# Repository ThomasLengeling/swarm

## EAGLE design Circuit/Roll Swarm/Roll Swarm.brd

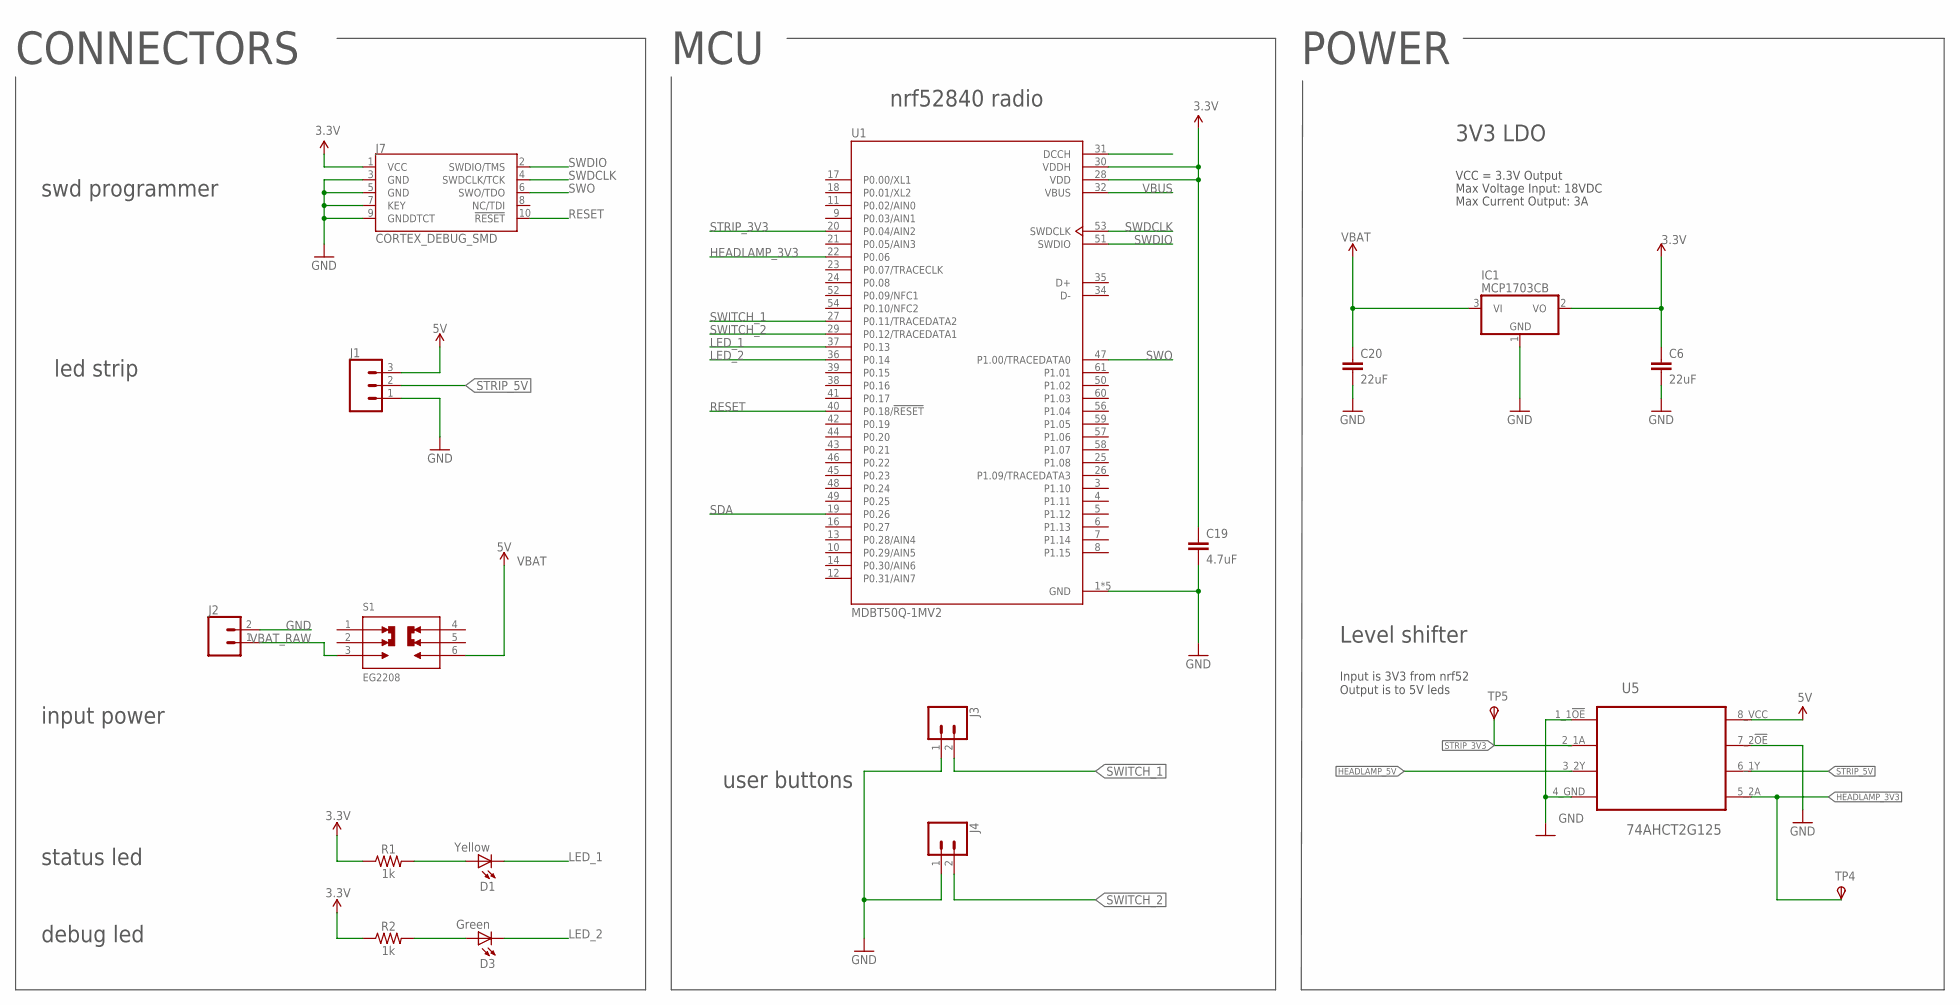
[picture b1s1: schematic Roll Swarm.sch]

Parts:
C6, C20: 22uF; 0805; DIGIKEY 490-10511-1-ND
C19: 4.7uF; 0603; DIGIKEY 399-3482-1-ND
D1: Yellow; LED-0603; DIGIKEY 350-4349-2-ND
D3: Green; LED-0603; DIGIKEY 754-1116-1-ND
IC1: MCP1703CB; SOT23; DIGIKEY AP2138N-3.3TRG1DICT-ND
J1: CONN_03LOCK_LONGPADS; 1X03_LOCK_LONGPADS; DIGIKEY S1111EC-03-ND
J2: CONN_02LOCK_LONGPADS; 1X02_LOCK_LONGPADS; DIGIKEY S1111EC-02-ND
J3, J4: CONN_02PTH4; 1X02_XTRA_BIG
J7: CORTEX_DEBUG_SMD; SAMTECH_FTSH-105-01; DIGIKEY SAM1161-05-ND
R1, R2: 1k; 0603; DIGIKEY RNCP0603FTD1K00CT-ND
S1: EG2208; SW_EG2208
TP4, TP5: TPSB1,27; B1,27
U1: MDBT50Q-1MV2; XCVR_MDBT50Q-1MV2
U5: 74AHCT2G125; VSSOP-8; DIGIKEY 1727-6544-1-ND‎

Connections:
3.3V: C6.1, C19.1, IC1.2 (VO), J7.1 (VCC), R1.1, R2.1, U1.28 (VDD), U1.30 (VDDH)
GND: C6.2, C19.2, C20.2, IC1.1 (GND), J1.1, J2.2, J3.1, J4.1, J7.3 (GND), J7.5 (GND), J7.7 (KEY), J7.9 (GNDDTCT), U1.1 (GND), U1.2 (GND), U1.15 (GND), U1.33 (GND), U1.55 (GND), U5.1_1!OE (1), U5.4_GND (4), U5.7_2!OE (7)
HEADLAMP_3V3: TP4.TP, U1.22 (P0.06), U5.5_2A (5)
HEADLAMP_5V: U5.3_2Y (3)
LED_1: D1.C, U1.37 (P0.13)
LED_2: D3.C, U1.36 (P0.14)
unnamed: D1.A, R1.2
unnamed: D3.A, R2.2
RESET: J7.10 (!RESET), U1.40 (P0.18/!RESET)
SDA: U1.19 (P0.26)
STRIP_3V3: TP5.TP, U1.20 (P0.04/AIN2), U5.2_1A (2)
STRIP_5V: J1.2, U5.6_1Y (6)
SWDCLK: J7.4 (SWDCLK/TCK), U1.53 (SWDCLK)
SWDIO: J7.2 (SWDIO/TMS), U1.51 (SWDIO)
SWITCH_1: J3.2, U1.27 (P0.11/TRACEDATA2)
SWITCH_2: J4.2, U1.29 (P0.12/TRACEDATA1)
SWO: J7.6 (SWO/TDO), U1.47 (P1.00/TRACEDATA0)
VBAT: C20.1, IC1.3 (VI), J1.3, S1.6, U5.8_VCC (8)
VBAT_RAW: J2.1, S1.3
VBUS: U1.32 (VBUS)

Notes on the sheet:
Max Voltage Input: 18VDC
Max Current Output: 3A
VCC = 3.3V Output
CONNECTORS
MCU
input power
led strip
3V3 LDO
POWER
status led
debug led
swd programmer
nrf52840 radio
Level shifter
Input is 3V3 from nrf52 Output is to 5V leds
user buttons

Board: 2 copper layers, 18 parts (2 on the bottom side), 17 nets, no tracks yet.

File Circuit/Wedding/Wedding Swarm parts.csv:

"Part";"Value";"Device";"Package";"Description";"DIGIKEY";"MPN";"OC_FARNELL";"OC_NEWARK";"PACKAGE";"POPULARITY";"PROD_ID";"SUPPLIER";"TP_SIGNAL_NAME";"VALUE";
"C6";"22uF";"22UF-0805-6.3V-20%";"0805";"22µF ceramic capacitors";"490-10511-1-ND";"";"";"";"";"";"CAP-08402";"";"";"22uF";
"C19";"4.7uF";"4.7UF0603";"0603";"4.7µF ceramic capacitors";"399-3482-1-ND";"";"";"";"";"";"CAP-08280";"";"";"4.7uF";
"C20";"22uF";"22UF-0805-6.3V-20%";"0805";"22µF ceramic capacitors";"490-10511-1-ND";"";"";"";"";"";"CAP-08402";"";"";"22uF";
"D1";"Yellow";"LED0603";"LED-0603";"LEDs";"350-4349-2-ND";"";"";"";"";"";"";"";"";"";
"D3";"Green";"LED0603";"LED-0603";"LEDs";"754-1116-1-ND";"";"";"";"";"";"";"";"";"";
"IC1";"MCP1703CB";"MCP1703CB";"SOT23";"250 mA, 16V, Low Quiescent Current LDO Regulator";"AP2138N-3.3TRG1DICT-ND";"";"";"";"";"19";"";"";"";"";
"J1";"";"CONN_03LOCK_LONGPADS";"1X03_LOCK_LONGPADS";"Multi connection point. Often used as Generic Header-pin footprint for 0.1 inch spaced/style header connections";"S1111EC-03-ND";"";"";"";"";"";"";"";"";"";
"J2";"";"CONN_02LOCK_LONGPADS";"1X02_LOCK_LONGPADS";"Multi connection point. Often used as Generic Header-pin footprint for 0.1 inch spaced/style header connections";"S1111EC-02-ND";"";"";"";"";"";"";"";"";"";
"J3";"";"CONN_02LOCK_LONGPADS";"1X02_LOCK_LONGPADS";"Multi connection point. Often used as Generic Header-pin footprint for 0.1 inch spaced/style header connections";"";"";"";"";"";"";"";"";"";"";
"J4";"";"CONN_02LOCK_LONGPADS";"1X02_LOCK_LONGPADS";"Multi connection point. Often used as Generic Header-pin footprint for 0.1 inch spaced/style header connections";"";"";"";"";"";"";"";"";"";"";
"J5";"";"CONN_02LOCK_LONGPADS";"1X02_LOCK_LONGPADS";"Multi connection point. Often used as Generic Header-pin footprint for 0.1 inch spaced/style header connections";"";"";"";"";"";"";"";"";"";"";
"J7";"CORTEX_DEBUG_SMD";"CORTEX_DEBUG_SMD";"SAMTECH_FTSH-105-01";"Cortex Debug Connector - 10 pin";"SAM1161-05-ND";"";"";"";"";"";"";"";"";"";
"R1";"1k";"1KOHM-0603-1/10W-1%";"0603";"1kΩ resistor";"RNCP0603FTD1K00CT-ND";"";"";"";"";"";"RES-07856";"";"";"1k";
"R2";"1k";"1KOHM-0603-1/10W-1%";"0603";"1kΩ resistor";"RNCP0603FTD1K00CT-ND";"";"";"";"";"";"RES-07856";"";"";"1k";
"TP1";"TPSB1,27";"TPSB1,27";"B1,27";"TEST PIN";"";"";"";"";"";"0";"";"";"";"";
"TP4";"TPSB1,27";"TPSB1,27";"B1,27";"TEST PIN";"";"";"";"";"";"0";"";"";"";"";
"TP5";"TPSB1,27";"TPSB1,27";"B1,27";"TEST PIN";"";"";"";"";"";"0";"";"";"";"";
"U3";"BC840M";"BC840M";"BC840M";"";"1914-BC840CT-ND";"";"";"";"";"";"";"";"";"";
"U5";"74AHCT2G125";"VSSOP-8_DEVICE";"VSSOP-8";"Dual bidirectional I2C-bus and SMBus voltage-level translator";"1727-6544-1-ND‎";"PCA9306DC,125";"-";"70R6429";"VSSOP-8";"";"";"NXP";"";"";

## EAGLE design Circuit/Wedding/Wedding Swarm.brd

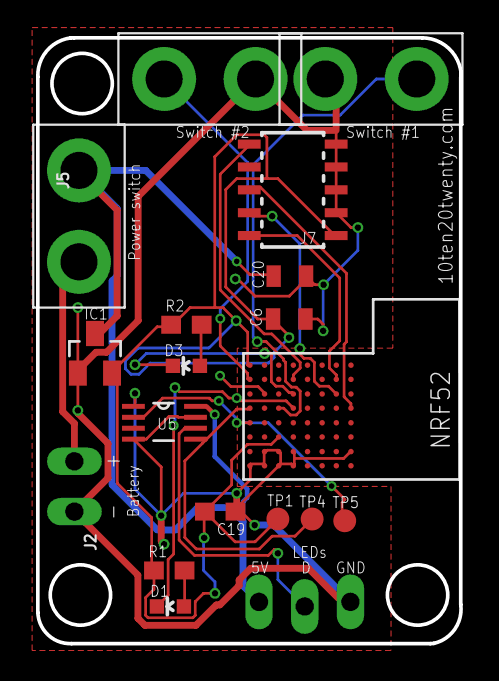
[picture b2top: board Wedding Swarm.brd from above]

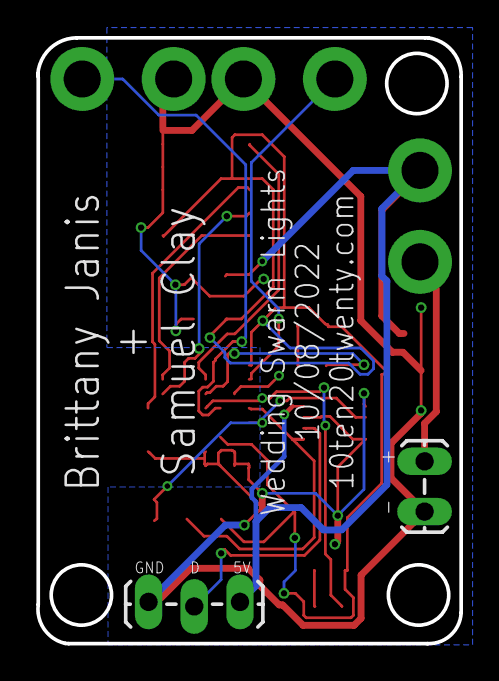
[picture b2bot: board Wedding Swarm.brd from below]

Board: 2 copper layers, 23.5 x 33.7 mm, 19 parts (2 on the bottom side), 17 nets.

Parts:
C6, C20: 22uF; 0805
C19: 4.7uF; 0603
D1: Yellow; LED-0603
D3: Green; LED-0603
IC1: MCP1703CB; SOT23
J1: 1X03_LOCK_LONGPADS
J2: 1X02_LOCK_LONGPADS
J3, J4, J5: 1X02_XTRA_BIG
J7: CORTEX_DEBUG_SMD; SAMTECH_FTSH-105-01
R1, R2: 1k; 0603
TP1, TP4, TP5: TPSB1,27; B1,27
U3: BC840M
U5: 74AHCT2G125; VSSOP-8

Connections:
3.3V: C6.1, C19.1, IC1.2, J7.1, R1.1, R2.1, TP1.TP, U3.A7, U3.F5
GND: C6.2, C19.2, C20.2, IC1.1, J1.1, J2.2, J3.1, J4.1, J7.3, J7.5, J7.7, J7.9, U3.G0, U3.G4, U3.G5, U3.G6, U3.H4, U3.H5, U3.H6, U3.H7, U5.1_1!OE, U5.4_GND, U5.7_2!OE
HEADLAMP_3V3: TP4.TP, U3.D7, U5.5_2A
LED_1: D1.C, U3.D4
LED_2: D3.C, U3.C4
unnamed: D1.A, R1.2
unnamed: D3.A, R2.2
RESET: J7.10, U3.B4
STRIP_3V3: TP5.TP, U3.E7, U5.2_1A
STRIP_5V: J1.2, U5.6_1Y
SWDCLK: J7.4, U3.C1
SWDIO: J7.2, U3.B1
SWITCH_1: J3.2, U3.D5
SWITCH_2: J4.2, U3.B7
SWO: J7.6, U3.D0
VBAT: C20.1, IC1.3, J1.3, J5.1, U5.8_VCC
VBAT_RAW: J2.1, J5.2

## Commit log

2022-08-13 Adding in wedding swarm circuit.
2022-08-14 Tinier size board, with new external buttons and switch.
2022-08-20 Moving radio in to accomodate two nrf52 module sizes.
2022-08-20 Finalizing board, switched all connectors to wide pads.
2022-09-03 Rev 2 of the wedding swarm board. Connected 5V and VBAT lines. Embiggened switches.
2022-09-09 Renaming swarm board to wedding swarm.
2022-09-09 Upping transmit power for BC840's tiny antenna.
2022-09-30 More colors.
2022-09-30 New alias for segger project.
2022-10-02 Start with purple fire.
2023-07-06 Adding roll swarm board with new radio module. Still needs new switch, new buttons, and better battery hookup.
2023-07-09 Adding new board-mount on/off switch.

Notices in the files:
parts and their libraries:
SparkFun-Connectors: Licensing: Creative Commons ShareAlike 4.0 International - https://creativecommons.org/licenses/by-sa/4.0
SparkFun-Capacitors: Licensing: CC v3.0 Share-Alike You are welcome to use this library for commercial purposes.
